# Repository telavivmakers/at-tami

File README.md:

ATtami עָלֵקדוּאִינו
=================

fork of littlewire AVR based Vusb dev board and various other efforts around the ATtiny85 <br>
more at [docs.telavivmakers.space/attami](https://docs.telavivmakers.space/attami)<br>

Schematics
===

board layout
===

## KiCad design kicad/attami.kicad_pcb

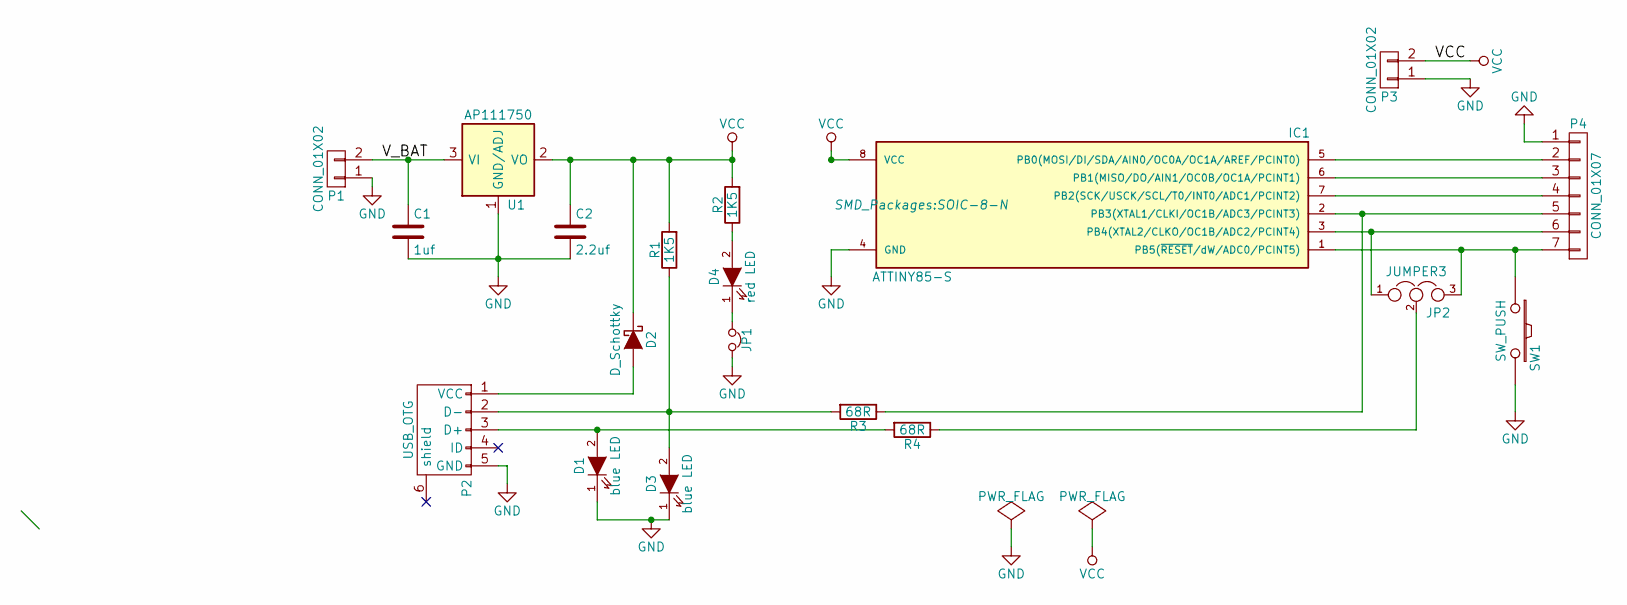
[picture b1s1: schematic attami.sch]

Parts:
C1: 1uf; C_0805
C2: 2.2uf; C_0805
D1, D3: blue LED; LED_0805
D2: D_Schottky; SOD-323
D4: red LED; LED_0805
IC1: ATTINY85-S; SOIC-8-N
JP1: Jumper_NC_Small; GS2
JP2: JUMPER3; GS3
P1, P3: CONN_01X02; Pin_Header_Straight_1x02
P2: USB_OTG; USB_Mini-B
P4: CONN_01X07; Pin_Header_Straight_1x07
R1, R2: 1K5; R_0805
R3, R4: 68R; R_0805
SW1: SW_PUSH; SW_SPST_EVQPE1
U1: AP111750; SOT-223

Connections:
/V_BAT: C1.1, P1.2, U1.3 (VI)
GND: C1.2, C2.2, D1.1 (K), D3.1 (K), IC1.4 (GND), JP1.2, P1.1, P2.5 (GND), P3.1, P4.1, SW1.2, U1.1 (GND/ADJ)
unnamed: D1.2 (A), P2.3 (D+), R4.2
unnamed: D2.2 (A), P2.1 (VCC)
unnamed: D3.2 (A), P2.2 (D-), R1.1, R3.2
unnamed: D4.1 (K), JP1.1
unnamed: D4.2 (A), R2.1
unnamed: IC1.1 (PB5(~RESET~/dW/ADC0/PCINT5)), JP2.3, P4.7, SW1.1
unnamed: IC1.2 (PB3(XTAL1/CLKI/OC1B/ADC3/PCINT3)), P4.5, R3.1
unnamed: IC1.3 (PB4(XTAL2/CLKO/OC1B/ADC2/PCINT4)), JP2.1, P4.6
unnamed: IC1.5 (PB0(MOSI/DI/SDA/AIN0/OC0A/OC1A/AREF/PCI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), P4.2
unnamed: IC1.6 (PB1(MISO/DO/AIN1/OC0B/OC1A/PCINT1)), P4.3
unnamed: IC1.7 (PB2(SCK/USCK/SCL/T0/INT0/ADC1/PCINT2)), P4.4
unnamed: JP2.2, R4.1
VCC: C2.1, D2.1 (K), IC1.8 (VCC), P3.2, R1.2, R2.2, U1.2 (VO), U1.4 (VO)

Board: 2 copper layers, 19 parts (0 on the bottom side), 15 nets, no tracks yet.

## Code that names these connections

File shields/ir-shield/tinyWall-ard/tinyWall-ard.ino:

// ATMEL ATTINY85 running @ 8MHz / ARDUINO **Zvi Schneider 12-May-2014**
//           		 +----\/---+
//  ADC0,  PB5, 	1|*           |8	VCC
//  ADC3,  PB3,	2|             |7	PB2,  ADC1
//  ADC2,  PB4,	3|             |6	PB1,
//  GND       	4|             |5	PB0,
//              		 +---------+
// http://telavivmakers.org/index.php/TinyWall
// https://github.com/telavivmakers/at-tami/tree/master/shields/ir-shield

#define my_milisec  76 // 76 interrupts equal 1 mili-sec (approximatly)
#define interval  100 //100 mili-sec interval between repetetive code transmitions
volatile long interrups_counter = 0;
byte virtual_wall = B10100010; // ROOMAs virtual wall code
int one_milisec = my_milisec;
int three_milisec = my_milisec * 3;

ISR (TIM0_COMPA_vect) { // interrupt service routine
  interrups_counter +=1;
}

void setup(){
  TCNT0 = 0; //initialize timer0 registers
  TCCR0A=0;
  TCCR0B=0;
  TCCR0A |=(1<<COM0A0); //Timer0 in toggle mode (Table 11-2)
  TCCR0A |=(1<<WGM01); //Timer0 in CTC mode (Table 11.5)
  TCCR0B |= (1 << CS00);// Prescaler (table 11.6, no prescaling)
  OCR0A=105-1; //CTC Compare value. with 8MHz clock and no prescaling this value will give interrupt every 13.125 micro-sec
  TIMSK |= 1<<OCIE0A; //enable timer0 OCR0A interrups
  SREG |= B10000000; //enable interrups
}

void loop(){
  while (interrups_counter < my_milisec*interval){ //wait interval miliseconds
  }
  interrups_counter = 0;
  xmitbyte(virtual_wall); //send one byte command to the ROOMBA
}

void xmitbyte(byte xmitdata){
  int i;
  int mark;
  int space;
  byte shift_one = B10000000;
  for (i = 0; i < 8; i++){
    if (xmitdata & shift_one){
      mark = three_milisec;
      space = one_milisec;
    }
    else {
      mark = one_milisec;
      space = three_milisec;
    }
    pinMode(PB0, OUTPUT); // mark, transmit IR pulses
    while (interrups_counter < mark){
    }
    interrups_counter = 0;
    pinMode(PB0, INPUT); // space, do not transmit IR pulses
    while (interrups_counter < space){
    }
    interrups_counter = 0;
    shift_one = shift_one >> 1;
  }
}

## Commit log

2014-03-22 eagle board layout
2014-03-26 fixed stuff
2014-04-08 fixed unrouted wires
2014-05-08 changed name and updated to rev4
2014-05-08 changed name and updated to rev04
2014-05-09 ver05 friday session
2014-05-15 ver07
    http://i.imgur.com/BFdtqUi.jpg
2014-05-15 ver07
    https://dl.dropboxusercontent.com/u/6430706/ShareX/2014/05/TAMI-ATTINY-V07.pdf
2014-05-25 ver08
    [zvi] switched the LDO to MIC5225. also changed some capacitors.
2014-05-25 ver 09
    [zvi] changed the schematics. MIC5205 is in together with its capacitor C3.
    The MIC5205 has two drawbacks:
    a. No guaranteed behavior for Vin < 5.5 V.
    b. No guaranteed behavior regarding reverse leakage.
    For applications with external supply greater than 5.5V there is no problem.
    We will have to test the reverse current issue when operating on USB 5V without external supply.
2014-06-02 ver 12
2014-06-04 ver 15b
2014-06-04 ver 15b
    this could be printed....
2014-06-04 ver 15c
    curved and fixed overlaps
    used DRU rules by OSHpark
    https://oshpark.com/guidelines
2014-06-04 ver 15c
    no change
2014-06-07 15b-04
    almost done
2014-06-07 15b-03
2014-06-12 ver 15b05
    now the polygon back silkscreen logo placed correctly, ready for panalizing(!)
2014-06-12 15b06
    because of sobbing of online gerber checker
    https://www.freedfm.com/freedfm/0022376203858107/results/summary2.htm
    - enlarge fonts on silkscreen to min 5mil
    - removed some redundant polygons from bottom silk
2014-06-16 Create ATTAMI-Shield-template.sch
    template for shields
2014-06-16 Create ATTAMI-Shield-template.brd
    template for sheilds
2014-06-16 ver 16
    now with stock DOC_frame
2014-06-16 Create TAMI-oshpark-gerb274x.cam
    used for exporting ATtami for valid OSHpark gerber files
    its based on the sparkfun cam gerb274x file, but
    added outline output (.GKO)
    added layer 25 (tNames) to top silkscreen (.GTO)
    added layer 26 (bNames) to bottom silkscreen (.GBO)
2014-06-16 Delete Little-Wire.J+N.pro
    this is historical, we moved to a fresh design
    thanks littleWire for showing us the way
2014-06-16 reaplced pic with ver16
2014-07-01 ver 17
    changed the USB connector to the "official" package
    MOLEX - 47346-0001 - MICRO USB TYPE B
2014-07-01 ver 17
    changed usb connector
2014-08-29 sent to FAB
    geekcon edition, with coincell
2014-08-29 template for v17
2014-08-31 Update README.md
    changed baord to v17 geekcon edition
2014-09-07 fix floating pin
    major error in voltage regualtor (U1). enable pin was not connected to
    VBAT in GKx batch :(.
2014-09-07 expanded microusb pads
    also add OSHW logo
    and removed some drawings
2014-09-07 silkscreen
    added slinkscreen to pads on the bottom
    remove tiny text from TAMI logo
2014-09-07 added hebrew slang, will it work?
2014-09-07 updated pic to ver17b
    https://github.com/telavivmakers/at-tami/commit/445718143124147e8c1c812b3e7fddc0d333db01
2014-09-08 seocnd batch to fab
    zv additions
    Added + and gnd marking near the coin-cell legs on bottom side of the
    PCB.
    Made some legend changing on the schematic.
2014-10-02 ATTami version 0.00
    PB5 connected,
    Added version # on bnames layer
    disconnected usb shield from ground
2014-10-16 changed pic to rev0
2014-10-28 same shield, with added mounting holes and better naming based on ver 0.00
    based on attami ver 0.00
    https://github.com/telavivmakers/at-tami/commit/00271a633f93de088d04ac549667f0e04d0c47cf#diff-2c24cc5344d8d061ae0f0b1c47d7ba8a
2014-10-28 ignore temp eagle files
2014-10-28 servo shield - new
    also added names and labels on wires
2014-10-28 flipped servo power pins
2014-11-05 servo shield
2014-11-05 servi inverter
2014-11-06 servo shield-no invert :(
2014-11-24 midnight edition, 1x2 layout
    taking space of two ATTami (1800x900 mil) .
    leaving much place for silkscreen.
    power on the right, servos on the left
    no VCC pins on shield.
    bottom copper plate is no longer ground, its now V_BAT.
2014-11-24 rough layout change
    switched position of servos for better layout
2014-11-25 folders
2014-11-25 cleaned template shield
2014-11-25 WIP
    basing on http://elm-chan.org/works/sd8p/report.html
    | what cap and inductor to use?
2014-11-26 changes to cap and inductor
2014-11-26 V_BAT connect to charging circuit
2014-11-26 added pdf
2014-11-26 moved pdf of sounday shield
2014-11-30 removed unused layers from eagle project
2014-11-30 vector fonts, text change
2014-12-05 new tami logo
    using svg2poly.ulp
2014-12-07 more work on generic shield
    also added an SVG with TAMI logo
2014-12-11 a shield for the pololu stepper driver, basic idea of schema and layout
    the pinout of the eagle part is a total mess. need to make my own.
    notice the PB5/RESET pin trick
2014-12-14 added ATtami eagle part library
2014-12-14 cont work on stepper shield
    mostly done, could work if we agree on V_BAT to 12V
2014-12-15 updtae A4988 lib part
2014-12-15 choose eagle files
2014-12-16 addded 4pin header for 12+ and I2C, not routed
2014-12-16 fix switched pins in stepper lib
    1A <-> 1B
2014-12-16 updated wiring, needs review
2014-12-16 added layout png
2014-12-16 remove project file
2014-12-16 added schema pdf
2014-12-28 ccc working on legend
2014-12-29 plotter
2015-01-01 added nice attami logo
2015-01-02 removed unuised ID pin from micro usb connector
2015-01-02 added attiny85 devices
    from Atmel_By_element14_Batch_1-00.lbr via farnel
2015-01-02 moved all parts to ATtami lib, trimmed it
2015-01-03 updated layout
    including re-routing the EN-VIN connection on U1 and removing a few
    routes that allows for this design to work as a one layer board with a
    bit of work.
2015-01-03 updated logo for the ATtami
2015-01-04 small layout change
2015-01-04 re introduced the vias under the regulator
2015-01-04 moved ATtami logo to the shield example
2015-01-04 add 1x4 and 1x6 headers to the library
2015-01-04 added pin number on breakout header
2015-01-04 new shield (in progress)
2015-01-08 changes in trace width (8mil) and fine tune the aliexpress microusb packge
2015-01-08 new design with added AMS1117 voltage regulator
    with library reflecting the part
2015-01-10 start tutushield
2015-01-10 added MSGEQ7 to lib
2015-01-10 added msgeq7 + capacitor & resistors
2015-01-10 didn't save last time :\
2015-01-11 small rewire
2015-01-11 updated shield tamplete to only use ATtami lib parts
2015-01-11 layout fixing and pdf
2015-01-12 charge shield
2015-01-16 new serial shield
    around CH340G (CH340) ic
2015-01-16 simplfy
    this is a driver design we need a barebone onn with High Speed
    Optoisolator SOIC 16 , 60V 4A.
2015-01-16 added the pb5 as digitall/reset pin thing
    also text comments
2015-01-16 sorry, i mixed signals
2015-01-16 a version without the PB5 trick
    it might be a bit simpler but i think its worth it to stick to
    4af68e7c457e82ac5364ccc3b228164f2045e11b
2015-01-16 routed
    without the PB5
2015-01-16 done schema
2015-01-18 fix GND and VCC airwires
2015-01-19 an attami device added to lib
2015-01-19 Moved via because of DRC rules
    Moved via next to the main chip because of DRC rules and 'ratsnest'ed it
2015-01-21 tutu vectrozied
2015-01-22 Added Gitter badge
2015-01-24 added tutu logo and BMP file
2015-01-24 fixed vcc wire bugs
2015-01-24 added tutu images and caption
2015-01-24 added elecros gerber cam job for eagle
2015-01-27 ready to ship, nice low via count
2015-01-27 final schematics and board
2015-01-28 fixed sizes of silkscreen fonts (was smaller then 32mil)
2015-01-28 added directory with current pcb house rules for eagle
2015-01-28 removed pictures from tutu shield dir
2015-01-28 cleaning
2015-01-28 gitignore now works also on subfolders
2015-01-28 gitignore eagle jobs
2015-02-12 New look for "ATTAMI_BREAKOUT_SHIELD"
2015-02-25 new looks from zvi
2015-03-03 added zif to lib
2015-03-07 rewire the npn transistors
2015-03-09 fixed pwm misshap in tutu shield
2015-03-15 3state stepperdriver added (WIP)
2015-03-15 some addition to 3state driver udi
2015-03-17 mostly lib work
2015-04-03 fixed tutushield, needs review
2015-04-03 fixed some github problems. added the jumper to allow for midi out. intgrated the 2nd voltage regulator to make it cheap again
2015-04-03 pushed the pb5 wire a bit to the cneter
2015-04-07 fixed attami.lbr , taken correct attami template from high-voltage-programmer schema
2015-04-15 hl version
2015-04-16 Added remarks
2015-04-16 Some changes of the routing
2015-04-16 replaced PDF file
2015-04-16 hopefully didnt bork everything with zvi pull req
2015-04-16 new pdf with zvi remarks
2015-04-16 fixed pesky unconnected wires in jumper,, and removed value from jumer
2015-07-22 added kicad WIP folder
2015-07-22 10mil width traces and pushed the PB5 bottom trace up
2015-07-22 added gerbmerge oldie
2015-07-22 removed kicad, need to start again
2015-07-23 updated pdf
2015-07-23 new baord ready for panelizition in win32
2015-07-23 new gerber sent to be approved by pcb house #1 for 2015
2015-07-23 fixed some airwires in the board, and new panelize
2015-07-23 Update README.md
    new pics of board
2015-07-23 a versin without the fancy LDO and SOT0232 for the X1117
2015-07-30 moved power led jumper to top layer
2015-08-03 gerbering to fab
2015-08-03 ***sent to fab***
2015-08-08 removed generated gerber, will add from email to elecrow
2015-08-19 assmbly instructions
2015-08-19 assmbly instructions risze paper
2015-08-19 2x2 layout
2015-08-19 layout chage for D4
2015-08-19 plotter stencil
2015-08-19 new schema pdf
2015-10-10 correction to bat/gnd marking on top silk, it was reversed
2015-10-15 tweaked the usb pads, sending to fab
2015-10-30 new gerber reflecting correct gnd/vcc silkscreen. also refernace to zofz 3d gerber viewr
2015-11-04 added ir shiled from zvi
2015-11-04 added tinywall code
2015-11-04 links
2016-05-22 first post
2016-05-23 new lib
2016-08-24 ignore scr
2016-08-24 kicad schema, done!
2016-08-25 added project kicad extension
2016-08-25 first pcb spread, and pdf
2016-10-14 working on Cenon silkscreen
2016-10-14 pdf 1.4
2016-10-14 testing svg import to cenn
2016-10-14 flaten:
2016-10-22 diy halfbridge plans from hasadna/x_Bisv612ek%5B1-25%5D
2016-10-22 diyshield
2016-10-22 added udis brake, think thats the latest design 19.03.15
2016-11-13 udi_hbridge_w_opamps.png added
2017-07-13 added cam from sparkfun, pcbway uses them
